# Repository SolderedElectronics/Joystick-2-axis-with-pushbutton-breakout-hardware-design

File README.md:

# Joystick 2-axis with pushbutton breakout Hardware Design

## About the Product

|  |
| :----------------------------------------------------------: |
| [Buy Joystick 2-axis with pushbutton breakout](https://www.solde.red/333089) |

Joystick module is well known to all – it is identical to the one found in the PlayStation2 joystick. Whether you are making a game with a microcontroller or want more freedom while navigating a joystick module will come handy.

It reads X and Y position of the joystick knob (used for controlling) and whether the joystick is being pressed down. X and Y values are shown in the form of analog values while reading off if the joystick is pressed or not is shown in the form of digital value (HIGH/LOW; it has pull-up resistor).

---

## Repository Contents

This repository contains all design files for Joystick 2-axis with pushbutton breakout, organized as follows:

- **`CAD` folder**: Contains KiCAD design files, including:
  - Schematics
  - PCB layout
  - Panel PCB layout
  - Source 3D files in Fusion360, if any
  - All files are sorted by version with a detailed change log.
- **`OUTPUTS` folder**: Includes all production-ready files, such as:
  - Bill of Materials (BOM) and interactive BOM (iBOM)
  - PDF versions of schematics
  - 3D `.step` file of the board
  - 3D-printable models
  - Gerber files for PCB manufacturing
  - Image of the pinout of the board
  - Product image
  - Compliance, legal and generic sales documents

Refer to the `Change Log` in the CAD folder for details about updates between versions.

---

## Learn More About the Product

Beyond the repository, explore the following resources:

### Soldered Verify

The **Soldered Verify** system ensures every board you purchase from Soldered is fully functional. It also provides access to exclusive test data for your product. To get started, find the unique Soldered Verify ID on your product's packaging and enter the ID on the [Soldered Verify page](https://soldered.com/verify/) to access test results and additional product details.

### Soldered Community

Soldered Community is your go-to place for technical support. Our engineers track and answer all questions posted there, and it’s a great space for the maker community. Get answers to your questions and solutions for your challenges at [Soldered Community](https://soldered.com/community).

### solde.red

solde.red is an ultimate URL shortener and information hub. Access it by typing solde.red/ followed by your product SKU, e.g., [solde.red/333000](https://solde.red/333000), to find getting-started guides, datasheets, open-source hardware and software files, certifications, images, pinouts, and more. Read more about the shortener [here](https://solde.red/info/).

---

## Contributing

Contributions are welcome! Here’s how you can get involved:

- Submit pull requests to enhance the design or fix issues.
- Report bugs or problems by opening an issue.

We encourage community collaboration to make this product even better.

---

## About Soldered

[Soldered for Makers](https://soldered.com) specializes in designing and manufacturing electronic products tailored for enthusiasts, ranging from hobbyists to professionals. Our portfolio includes electronic boards, sensors, and actuators that are widely utilized in fields such as microelectronics, mechatronics, robotics, programming, and IoT. Every product we offer is designed in-house and built upon open-source hardware and software platforms. Proudly certified and manufactured within the European Union, our catalog likely includes the product you need for your project.

We complement these products with comprehensive tutorials and manuals, product descriptions, schematics, programming codes, and project examples. Our round-the-clock [customer and technical support](https://soldered.com/community) is available for all our products, irrespective of the sales channel. Soldered’s success and services reflect our maker community’s unwavering [trust](https://www.trustpilot.com/review/soldered.com), for which we are deeply grateful. Join our community and create using Soldered products.

---

## License

All Soldered open-source hardware (OSH) is under The TAPR Open Hardware License. Read more in the LICENSE file located in this repository.

**Disclaimer:**

No warranty - all designs in this repository are distributed in the hope that they will be useful, but without any warranty. They are provided "AS IS", therefore without warranty of any kind, either expressed or implied. The entire quality and performance of what you do with the contents of this repository are your responsibility. In no event Soldered Electronics will be liable for your damages, or losses, including any general, special, incidental, or consequential damage arising out of the use or inability to use the contents of this repository. 

---

## Have fun!

Thank you for your support from your fellow makers at Soldered Electronics.

Happy Making!

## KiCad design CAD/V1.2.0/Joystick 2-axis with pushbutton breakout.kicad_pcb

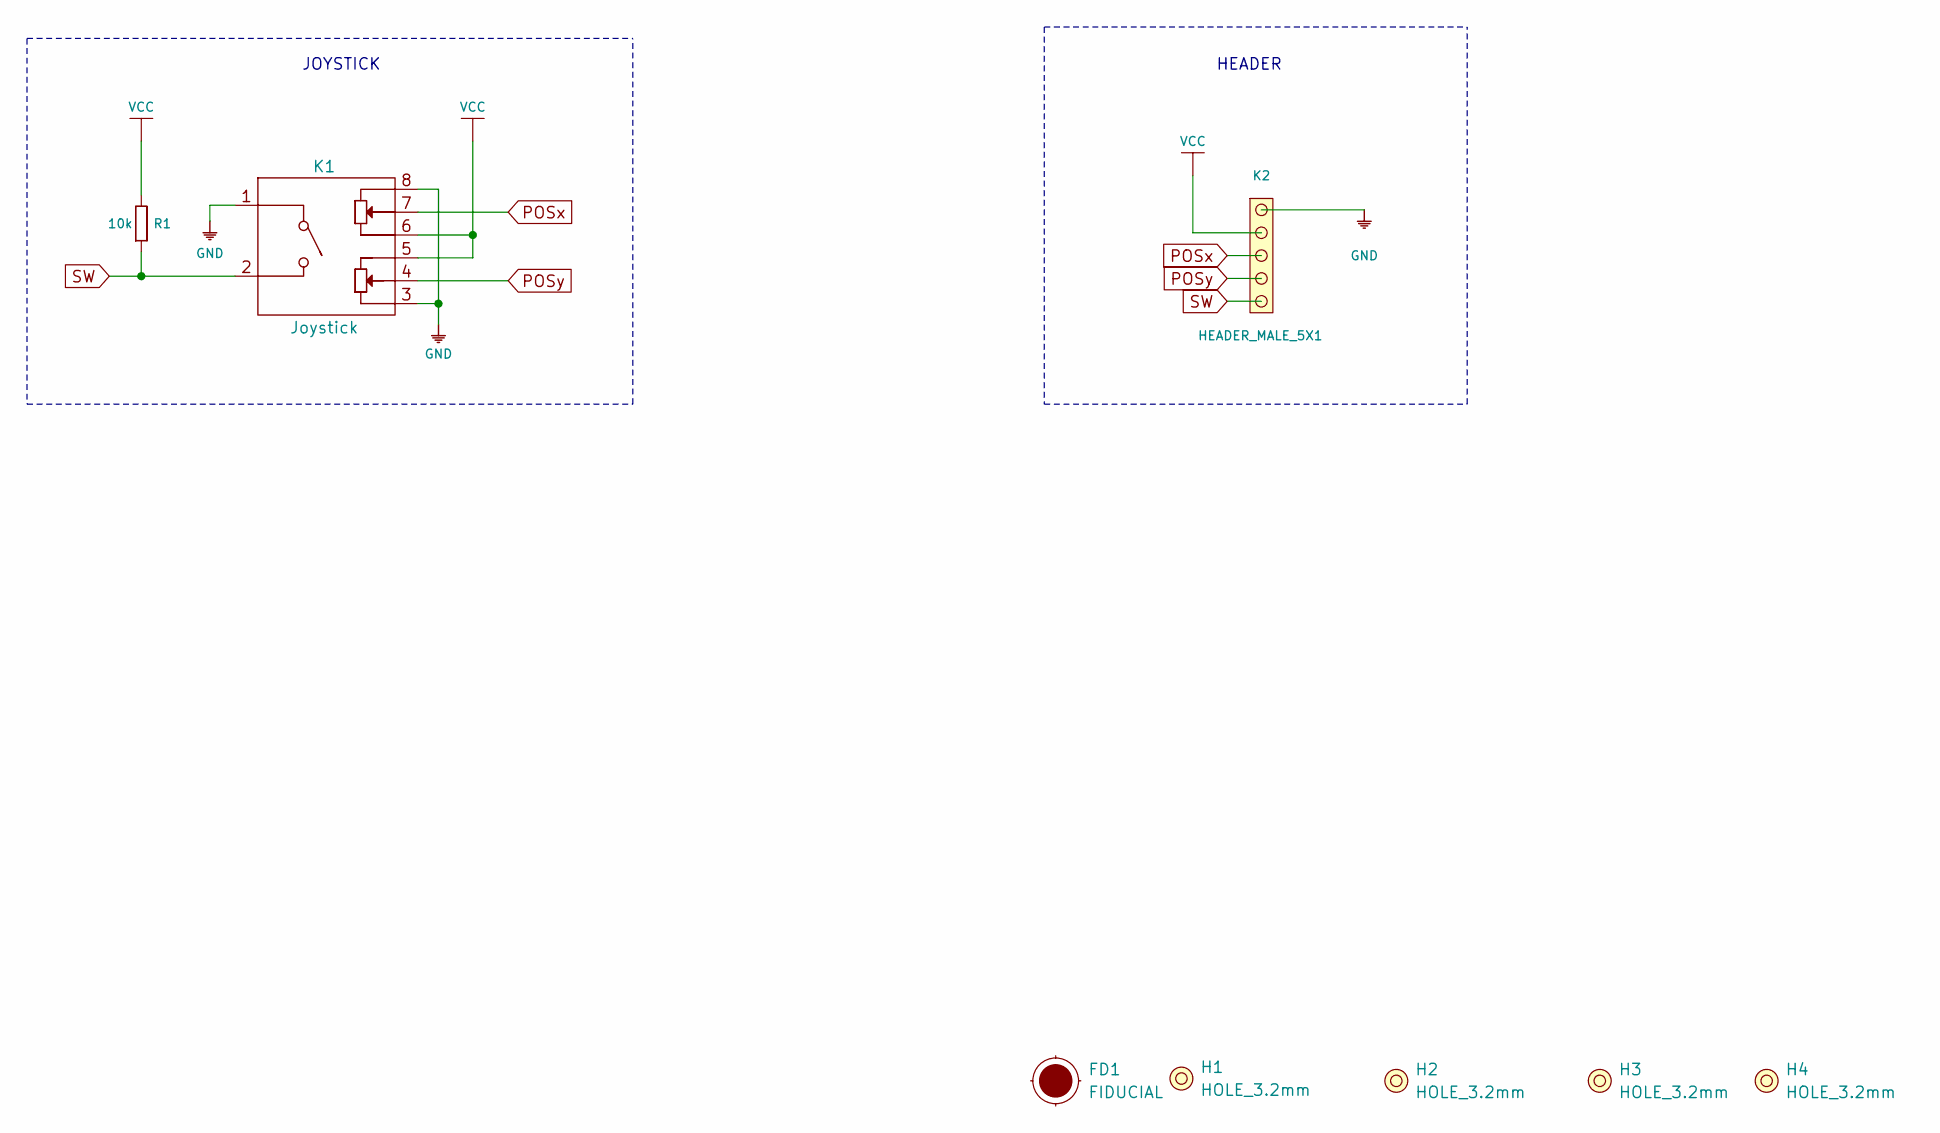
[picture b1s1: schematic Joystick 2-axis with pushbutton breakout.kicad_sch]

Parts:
FD1: FIDUCIAL; FIDUCIAL_23
H1, H2, H3, H4: HOLE_3.2mm
K1: Joystick; joystick
K2: HEADER_MALE_5X1
R1: 10k; 0603R

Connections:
GND: K1.1, K1.3, K1.8, K2.5
POSx: K1.7, K2.3
POSy: K1.4, K2.2
SW: K1.2, K2.1, R1.1
VCC: K1.5, K1.6, K2.4, R1.2

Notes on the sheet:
JOYSTICK
HEADER

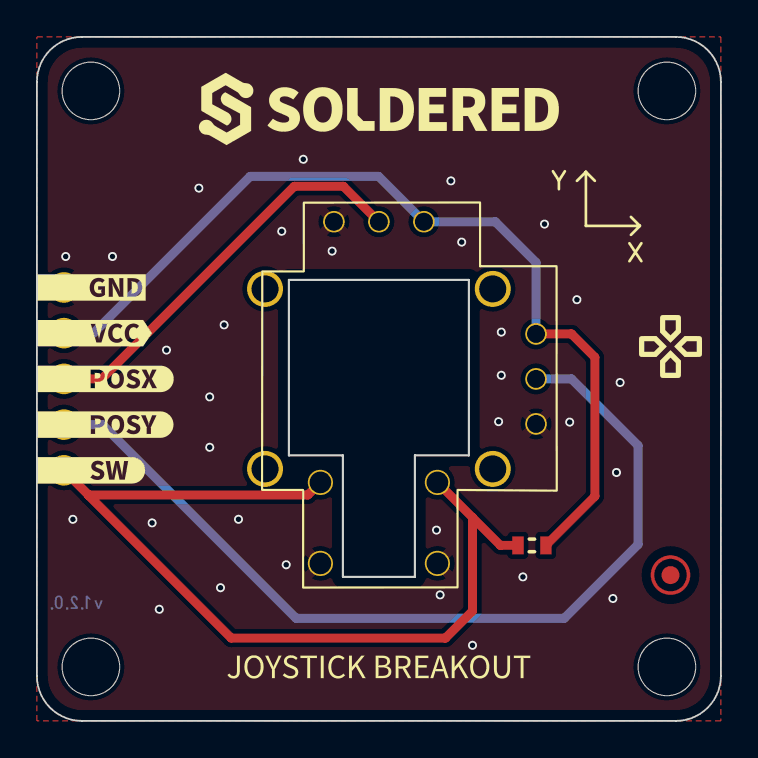
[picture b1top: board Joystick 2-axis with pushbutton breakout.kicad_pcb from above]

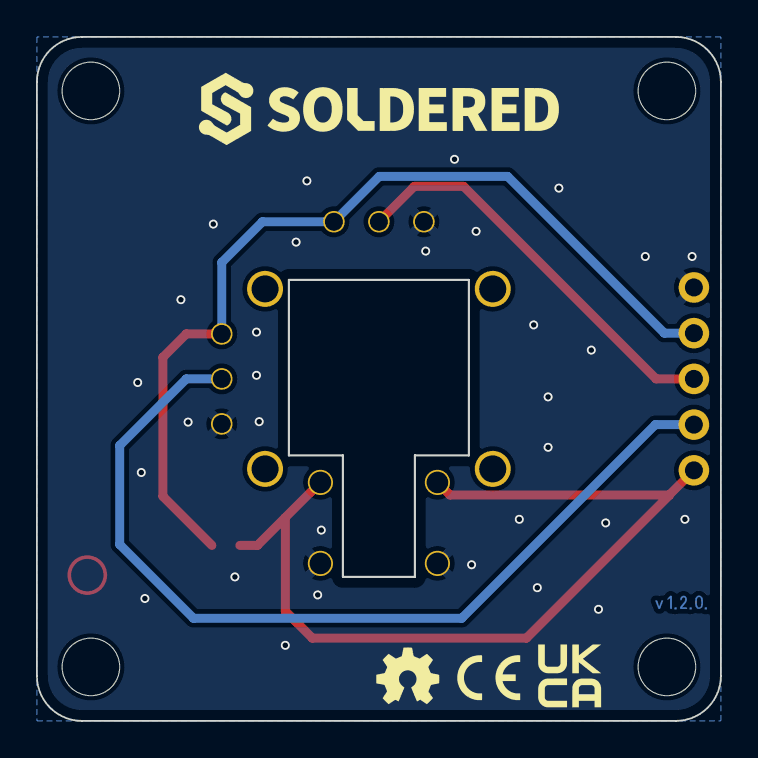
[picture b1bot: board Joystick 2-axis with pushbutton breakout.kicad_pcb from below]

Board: 2 copper layers, 38.0 x 38.0 mm, 14 parts (2 on the bottom side), 5 nets.

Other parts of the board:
kibuzzard-668288C6: G***; kibuzzard-668288C6
kibuzzard-668289A6: G***; kibuzzard-668289A6
kibuzzard-6682892F: G***; kibuzzard-6682892F
kibuzzard-66828953: G***; kibuzzard-66828953
kibuzzard-66828977: G***; kibuzzard-66828977
kibuzzard-66828995: G***; kibuzzard-66828995

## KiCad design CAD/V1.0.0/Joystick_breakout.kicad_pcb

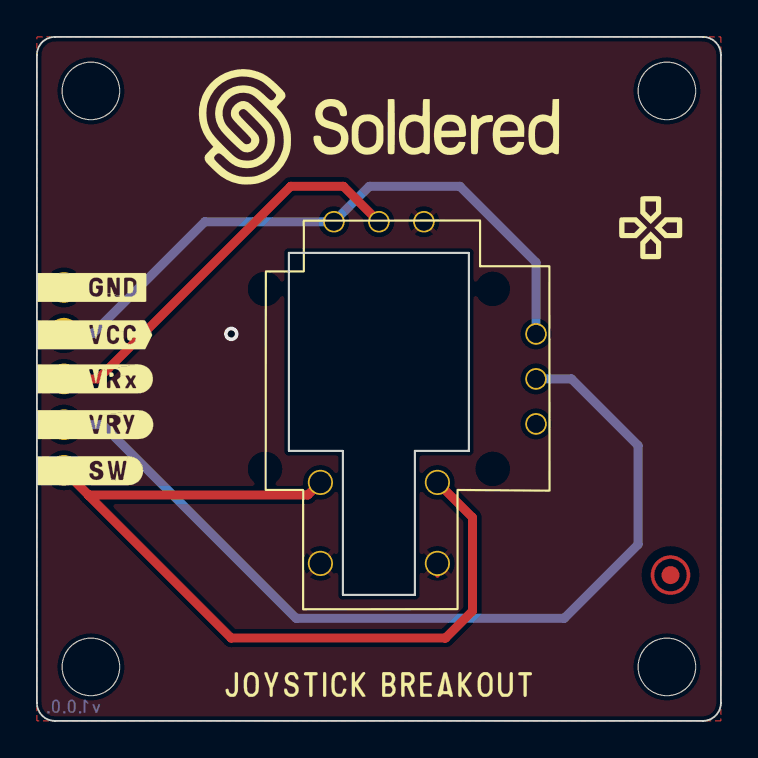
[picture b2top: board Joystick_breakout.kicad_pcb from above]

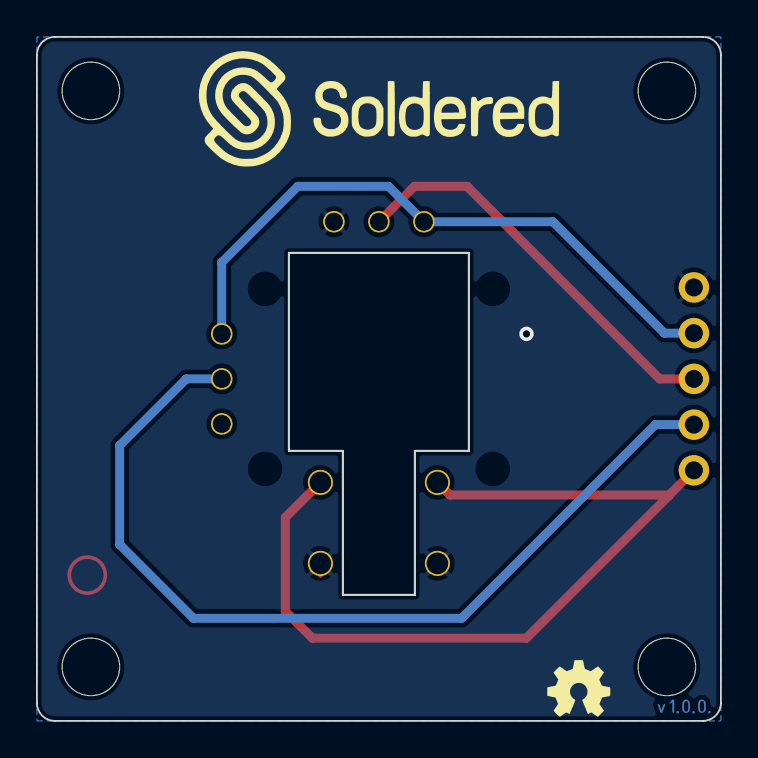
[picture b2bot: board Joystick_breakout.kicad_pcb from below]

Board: 2 copper layers, 38.0 x 38.0 mm, 8 parts (2 on the bottom side), 5 nets.

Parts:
FD1: FIDUCIAL; FIDUCIAL_23
H1, H2, H3, H4: HOLE_3.2mm
K1: Joystick; joystick
K2: HEADER_MALE_5X1
Ref**: Val**; Version1.0.0.

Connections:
GND: K1.1, K1.6, K2.5
SW: K1.2, K2.1
VCC: K1.5, K1.8, K2.4
VRx: K1.7, K2.3
VRy: K1.4, K2.2

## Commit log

2022-08-06 Updating open source files.
